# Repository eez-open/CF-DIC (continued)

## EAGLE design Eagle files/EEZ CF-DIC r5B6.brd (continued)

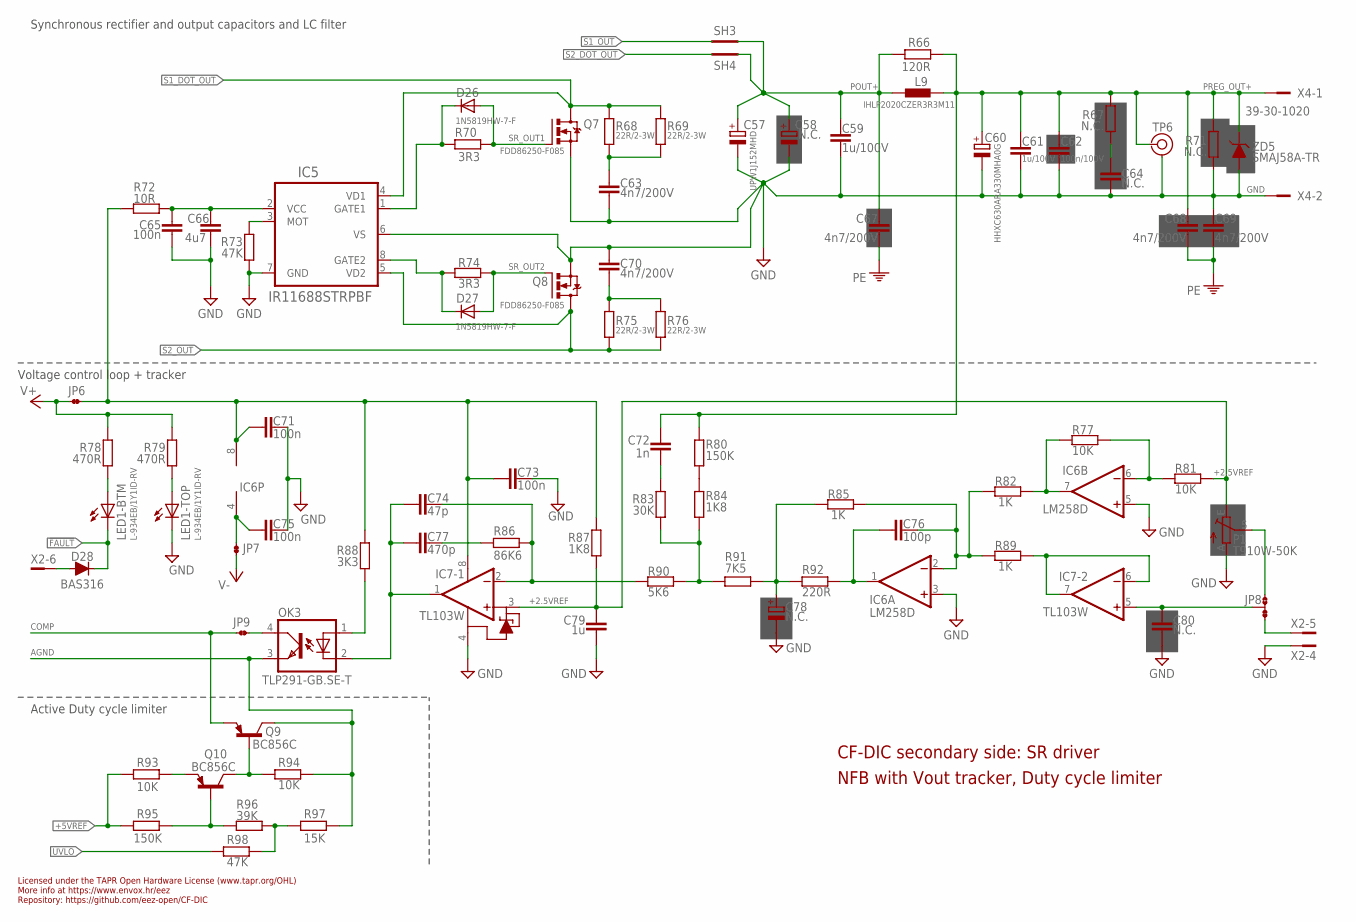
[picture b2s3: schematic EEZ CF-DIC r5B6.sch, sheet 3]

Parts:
C57: UPW1J152MHD; ECAP7.5/18-H35.5-2A
C58: N.C.; ECAP7.5/18
C59, C61: 1u/100V; C1206
C60: HHXC630ARA330MHA0G; CAPAE830X1050N
C62: 100n/100V; C1206
C63, C67, C68, C69, C70: 4n7/200V; C1206
C64: N.C.; C1206
C65, C71, C73, C75: 100n; C0603
C66: 4u7; C1206
C72: 1n; C0805
C74: 47p; C0805
C76: 100p; C0805
C77: 470p; C0805
C78: N.C.; EC1206
C79: 1u; C0805
C80: N.C.; C0805
D26, D27: 1N5819HW-7-F; SOD323-W
D28: BAS316; SOD323-R
IC5: IR11688STRPBF; SO8
IC6: LM258D; SOIC127P600X173-8N
IC7: TL103W; SOIC127P600X173-8N
JP6, JP7, JP9: JP2-NOCUT
JP8: JP3-CUT
L9: IHLP2020CZER3R3M11; IHLP-2020BZ-11
LED1: L-934EB/1Y1ID-RV; L-934EB
OK3: TLP291-GB.SE-T; SO4
P1: T910W-50K; S64W
Q7, Q8: FDD86250-F085; TO263
Q9, Q10: BC856C; SOT23-BEC
R66: 120R; R0805
R67: N.C.; R1210
R68, R69, R75, R76: 22R/2-3W; R2512
R70, R74: 3R3; R0805
R71: N.C.; R2512
R72: 10R; R0805
R73, R98: 47K; R0805
R77, R81, R93, R94: 10K; R0805
R78, R79: 470R; R0805
R80, R95: 150K; R0805
R82, R85, R89: 1K; R0805
R83: 30K; R0805
R84, R87: 1K8; R0805
R86: 86K6; R0805
R88: 3K3; R0805
R90: 5K6; R0805
R91: 7K5; R0805
R92: 220R; R0805
R96: 39K; R0805
R97: 15K; R0805
SH3, SH4: SHORTNOHOLE; SHORT_NOHOLE
TP6: TEST_POINT-2; TP_1.1MM_2
X2: 22-05-7095; SPOX_22-05-7095
X4: 39-30-1020; MINIFIT_39301020
ZD5: SMAJ58A-TR; DO214AC

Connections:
!FAULT: D28.C, LED1.BC (C); also elsewhere on the board
+2.5VREF: C79.1, IC7.3 (+IN1), P1.E, R81.2, R87.1
+5VREF: R93.1, R95.1; also elsewhere on the board
AGND: OK3.3 (EMIT), Q9.C, R94.2, R97.2; also elsewhere on the board
COMP: JP9.1, Q9.E; also elsewhere on the board
GND: C57.-, C58.-, C59.2, C60.-, C61.2, C62.2, C63.2, C64.1, C65.2, C66.2, C69.1, C70.2, C71.2, C73.2, C75.2, C78.-, C79.2, C80.2, IC5.6 (VS), IC5.7 (GND), IC6.3 (+IN), IC6.5 (+IN), IC7.4 (VCC-), LED1.TC (C), P1.A, Q7.2 (S), Q8.2 (S), R71.1, R73.2, TP6.GND, X2.4, X4.2, ZD5.A; also elsewhere on the board
unnamed: D28.A, X2.6
unnamed: C64.2, R67.1
unnamed: C77.2, R86.2
unnamed: C74.2, IC7.2 (-IN1), R86.1, R90.1
unnamed: LED1.TA (A), R79.2
unnamed: R80.1, R84.2
unnamed: LED1.BA (A), R78.2
unnamed: IC5.3 (MOT), R73.1
unnamed: C72.2, R83.2
unnamed: C75.1, IC6.4 (V-), JP7.1
unnamed: JP9.2, OK3.4 (COL)
unnamed: C71.1, C73.1, IC6.8 (V+), IC7.8 (VCC+), JP6.2, R72.1, R87.2, R88.2
unnamed: R83.1, R84.1, R90.2, R91.2
unnamed: IC6.7 (OUT), R77.1, R82.2
unnamed: C80.1, IC7.5 (+IN), JP8.COM
unnamed: JP8.NO, P1.S
unnamed: Q9.B, Q10.C, R94.1
unnamed: Q10.E, R93.2
unnamed: C76.2, IC6.2 (-IN), R82.1, R85.2, R89.1
unnamed: C63.1, R68.2, R69.2
unnamed: C70.1, R75.2, R76.2
unnamed: R96.2, R97.1, R98.1
unnamed: Q10.B, R95.2, R96.1
unnamed: D26.C, IC5.1 (GATE1), R70.2
unnamed: D27.C, IC5.8 (GATE2), R74.2
unnamed: C74.1, C77.1, IC7.1 (OUT1), OK3.2 (C)
unnamed: IC6.6 (-IN), R77.2, R81.1
unnamed: C76.1, IC6.1 (OUT), R92.2
NFB_OFFSET: C78.+, R85.1, R91.1, R92.1
OK_A: OK3.1 (A), R88.1
PE: C67.2, C68.2, C69.2; also elsewhere on the board
POUT+: C57.+, C58.+, C59.1, C67.1, L9.1, R66.1, SH3.P$2 (GND_B), SH4.P$1 (GND_A)
PREG_OUT+: C60.+, C61.1, C62.1, C68.1, C72.1, L9.2, R66.2, R67.2, R71.2, R80.2, TP6.TIP, X4.1, ZD5.C; also elsewhere on the board
S1_DOT_OUT: IC5.4 (VD1), Q7.3 (D), R68.1, R69.1; also elsewhere on the board
S1_OUT: SH3.P$1 (GND_A); also elsewhere on the board
S2_DOT_OUT: SH4.P$2 (GND_B); also elsewhere on the board
S2_OUT: IC5.5 (VD2), Q8.3 (D), R75.1, R76.1; also elsewhere on the board
SR_OUT1: D26.A, Q7.1 (G), R70.1
SR_OUT2: D27.A, Q8.1 (G), R74.1
SYNC_VCC: C65.1, C66.1, IC5.2 (VCC), R72.2
UVLO: R98.2; also elsewhere on the board
U_CTRL: JP8.NC, X2.5
U_MON1: IC7.6 (-IN), IC7.7 (OUT), R89.2
V+: JP6.1, R78.1, R79.1; also elsewhere on the board
V-: JP7.2; also elsewhere on the board

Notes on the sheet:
Licensed under the TAPR Open Hardware License (www.tapr.org/OHL)
Repository: https://github.com/eez-open/CF-DIC
More info at https://www.envox.hr/eez
CF-DIC secondary side: SR driver
NFB with Vout tracker, Duty cycle limiter
Voltage control loop + tracker
Synchronous rectifier and output capacitors and LC filter
Active Duty cycle limiter

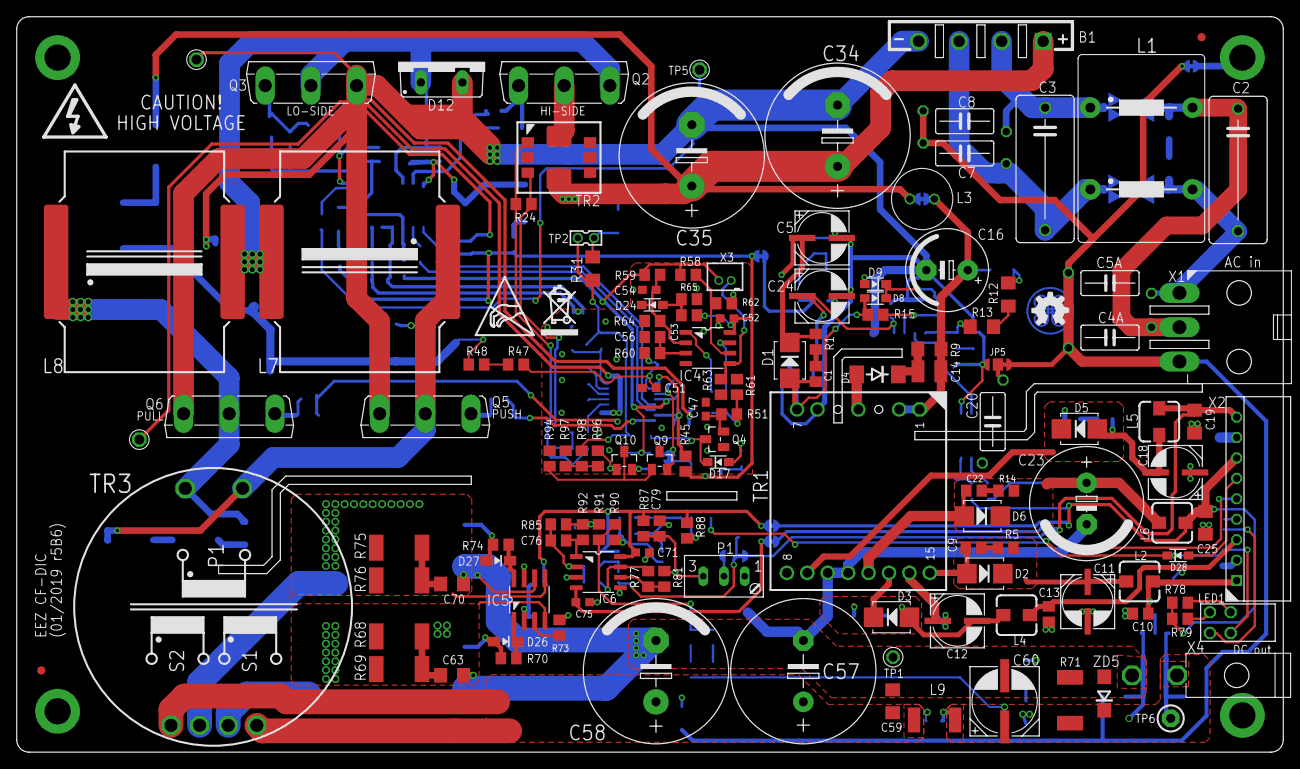
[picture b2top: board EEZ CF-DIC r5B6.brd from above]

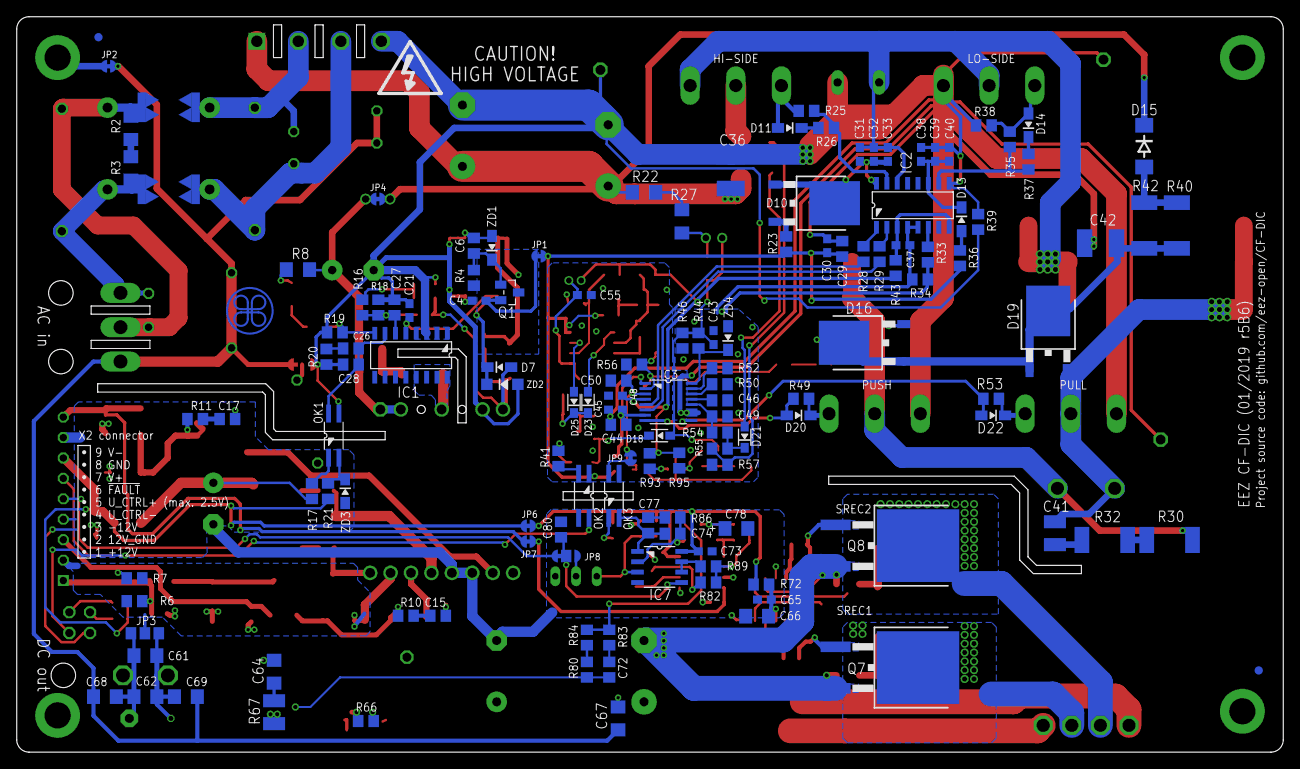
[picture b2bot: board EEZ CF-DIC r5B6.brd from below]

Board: 2 copper layers, 155.0 x 90.0 mm, 278 parts (137 on the bottom side), 147 nets.

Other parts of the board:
EEZ_SIGNATURE: SIGNATURESMALL; SIGNATURE_5MM
U$2: RECYCLE_BIN1/8
U$4: ESD_SYMBOL

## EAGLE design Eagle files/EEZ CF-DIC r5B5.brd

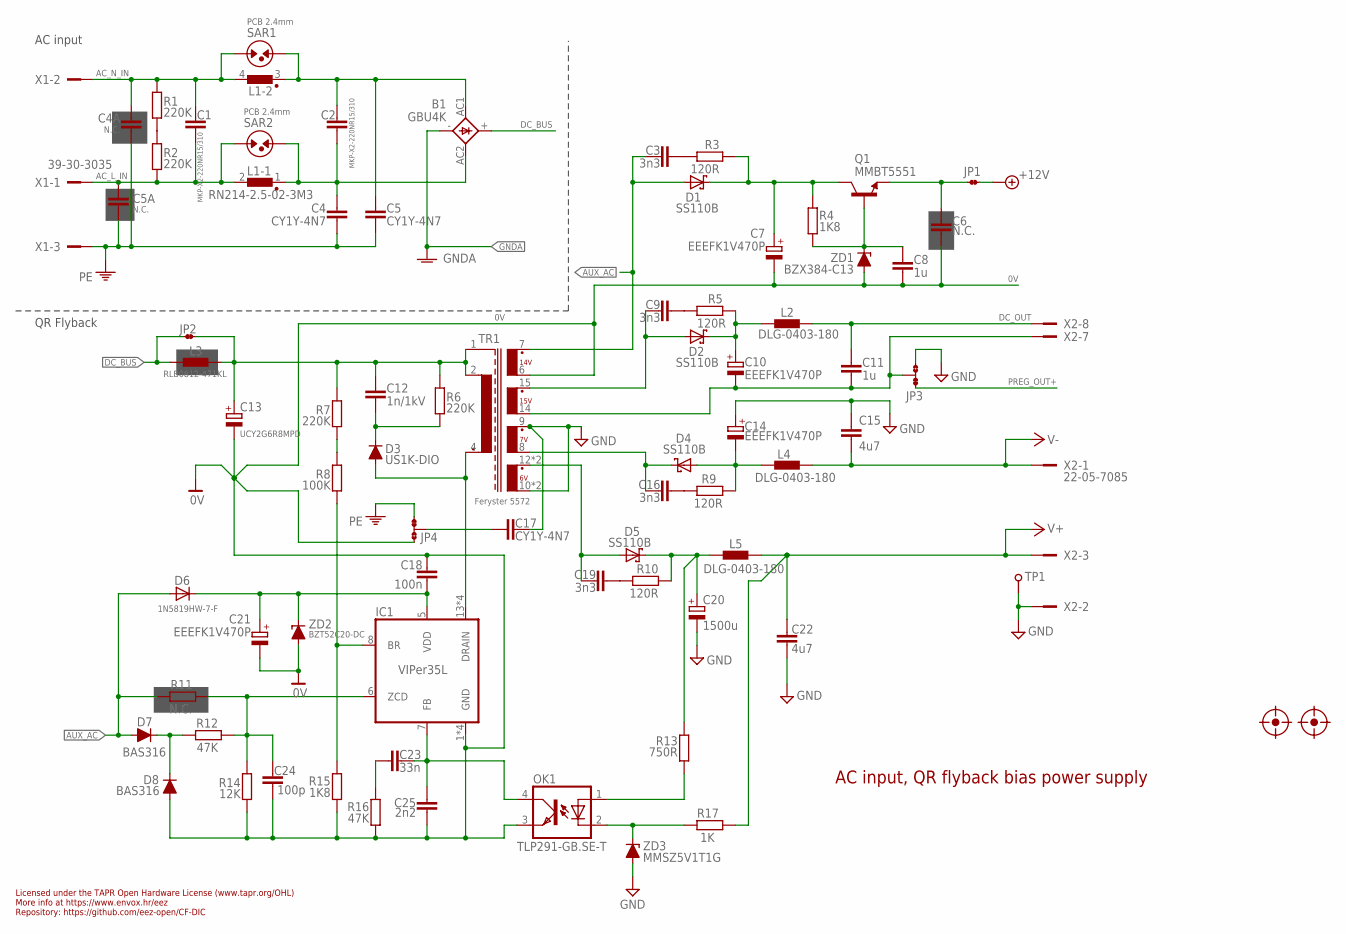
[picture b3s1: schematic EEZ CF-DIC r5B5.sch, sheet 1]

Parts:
B1: GBU4K; GBU4K_CRE
C1, C2: MKP-X2-220NR15/310; C150-072X183
C3, C9, C16, C19: 3n3; C0805
C4, C5, C17: CY1Y-4N7; CY075-032X103
C4A: N.C.; CY075-032X103-ROTATED
C5A: N.C.; CY075-032X103
C6: N.C.; C0603
C7, C10, C14, C21: EEEFK1V470P; CAPAE660X610N
C8, C11: 1u; C0805
C12: 1n/1kV; C1210
C13: UCY2G6R8MPD; ECAP5/10.5
C15, C22: 4u7; C1206
C18: 100n; C0603
C20: 1500u; ECAP5/13
C23: 33n; C0805
C24: 100p; C0805
C25: 2n2; C0805
D1, D2, D4, D5: SS110B; SMB
D3: US1K-DIO; DO214AA
D6: 1N5819HW-7-F; SOD323-W
D7, D8: BAS316; SOD323-R
FM1, FM2: FIDUCIAL_2; FIDUCIAL_DUAL
IC1: VIPer35L; SOIC-16
JP1, JP2: JP2-NOCUT
JP3, JP4: JP3-CUT
L1: RN214-2.5-02-3M3; RN214; FARNELL 1191518
L2, L4, L5: DLG-0403-180; DE0403
L3: RLB0812-471KL; FERSYTER_DSZ6
OK1: TLP291-GB.SE-T; SO4
Q1: MMBT5551; SOT23-BEC
R1, R2, R6, R7: 220K; R1206
R3, R5, R9, R10: 120R; R0805
R4, R15: 1K8; R0805
R8: 100K; R0805
R11: N.C.; R0805
R12, R16: 47K; R0805
R13: 750R; R0805
R14: 12K; R0805
R17: 1K; R0805
SAR1, SAR2: PCB 2.4mm; PCB-SAR_2.4MM
TP1: PCB_TEST_TABSHIELD; PCB_SHIELD_TAB
TR1: Feryster 5572; FERYSTER_5572
X1: 39-30-3035; MINIFIT_6659-3_CRE
X2: 22-05-7085; SPOX_22-05-7085
ZD1: BZX384-C13; SOD323-W
ZD2: BZT52C20-DC; SOD123
ZD3: MMSZ5V1T1G; SOD323-W

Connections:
0V: C6.2, C7.2 (-), C8.2, C13.-, C18.1, C21.2 (-), C24.2, C25.2, D8.A, IC1.1 (GND), IC1.2 (GND), IC1.3 (GND), IC1.4 (GND), JP4.NO, OK1.3 (EMIT), R14.1, R15.2, R16.2, TR1.6 (S_BIAS), ZD1.A, ZD2.A; also elsewhere on the board
6VAC: C19.2, D5.A, TR1.12 (S1_DOT), TR1.13 (S1_DOT)
7VAC: C16.2, D4.C, TR1.8 (S2)
15VAC: C9.2, D2.A, TR1.15 (S3_DOT)
+6V_REC: C20.+, D5.C, L5.1, R10.1, R13.1
+12V: JP1.2; also elsewhere on the board
+15V_REC: C10.1 (+), D2.C, L2.1, R5.1
-7V_REC: C14.2 (-), D4.A, L4.1, R9.1
-15V: C10.2 (-), C11.2, JP3.COM, TR1.14 (S3), X2.7
AC_L_IN: C1.2, C5A.2, L1.2, R2.2, SAR2.1, X1.1
AC_N_IN: C1.1, C4A.2, L1.4 (2), R1.1, SAR1.1, X1.2
AUX_AC: C3.2, D1.A, D6.A, D7.A, R11.2, TR1.7 (S_BIAS_DOT)
AUX_REC: C7.1 (+), D1.C, Q1.C, R3.1, R4.1
DC_BUS: B1.+, JP2.1, L3.P$1 (1); also elsewhere on the board
DC_OUT: C11.1, L2.2, X2.8
FB2: OK1.2 (C), R17.1, ZD3.C
GND: C14.1 (+), C15.1, C17.2, C20.-, C22.2, JP3.NO, TP1.1, TR1.9 (S2_DOT), TR1.10 (S1), TR1.11 (S1), X2.2, ZD3.A; also elsewhere on the board
GNDA: B1.-; also elsewhere on the board
unnamed: C17.1, JP4.COM
unnamed: IC1.8 (BR), R8.2, R15.1
unnamed: C6.1, JP1.1, Q1.E
unnamed: C18.2, C21.1 (+), D6.C, IC1.5 (VDD), ZD2.C
unnamed: R1.2, R2.1
unnamed: B1.AC1, C2.1, C5.2, L1.3 (1), SAR1.2
unnamed: B1.AC2, C2.2, C4.2, L1.1, SAR2.2
unnamed: R7.2, R8.1
unnamed: C8.1, Q1.B, R4.2, ZD1.C
unnamed: OK1.1 (A), R13.2
unnamed: C12.2, D3.C, R6.2
unnamed: C23.2, C25.1, IC1.7 (FB), OK1.4 (COL)
unnamed: C9.1, R5.2
unnamed: C3.1, R3.2
unnamed: C24.1, IC1.6 (ZCD), R11.1, R12.1, R14.2
unnamed: C16.1, R9.2
unnamed: C19.1, R10.2
unnamed: C23.1, R16.1
unnamed: D7.C, D8.C, R12.2
PE: C4.1, C4A.1, C5.1, C5A.1, JP4.NC, X1.3; also elsewhere on the board
PREG_OUT+: JP3.NC; also elsewhere on the board
V+: C22.1, L5.2, R17.2, X2.3; also elsewhere on the board
V-: C15.2, L4.2, X2.1; also elsewhere on the board
VIPER+: C12.1, C13.+, JP2.2, L3.P$2 (2), R6.1, R7.1, TR1.1 (SHIELD), TR1.2
VIPER_D: D3.A, IC1.13 (DRAIN), IC1.14 (DRAIN), IC1.15 (DRAIN), IC1.16 (DRAIN), TR1.4 (P2_DOT)

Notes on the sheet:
Licensed under the TAPR Open Hardware License (www.tapr.org/OHL)
Repository: https://github.com/eez-open/CF-DIC
More info at https://www.envox.hr/eez
AC input, QR flyback bias power supply
QR Flyback
AC input

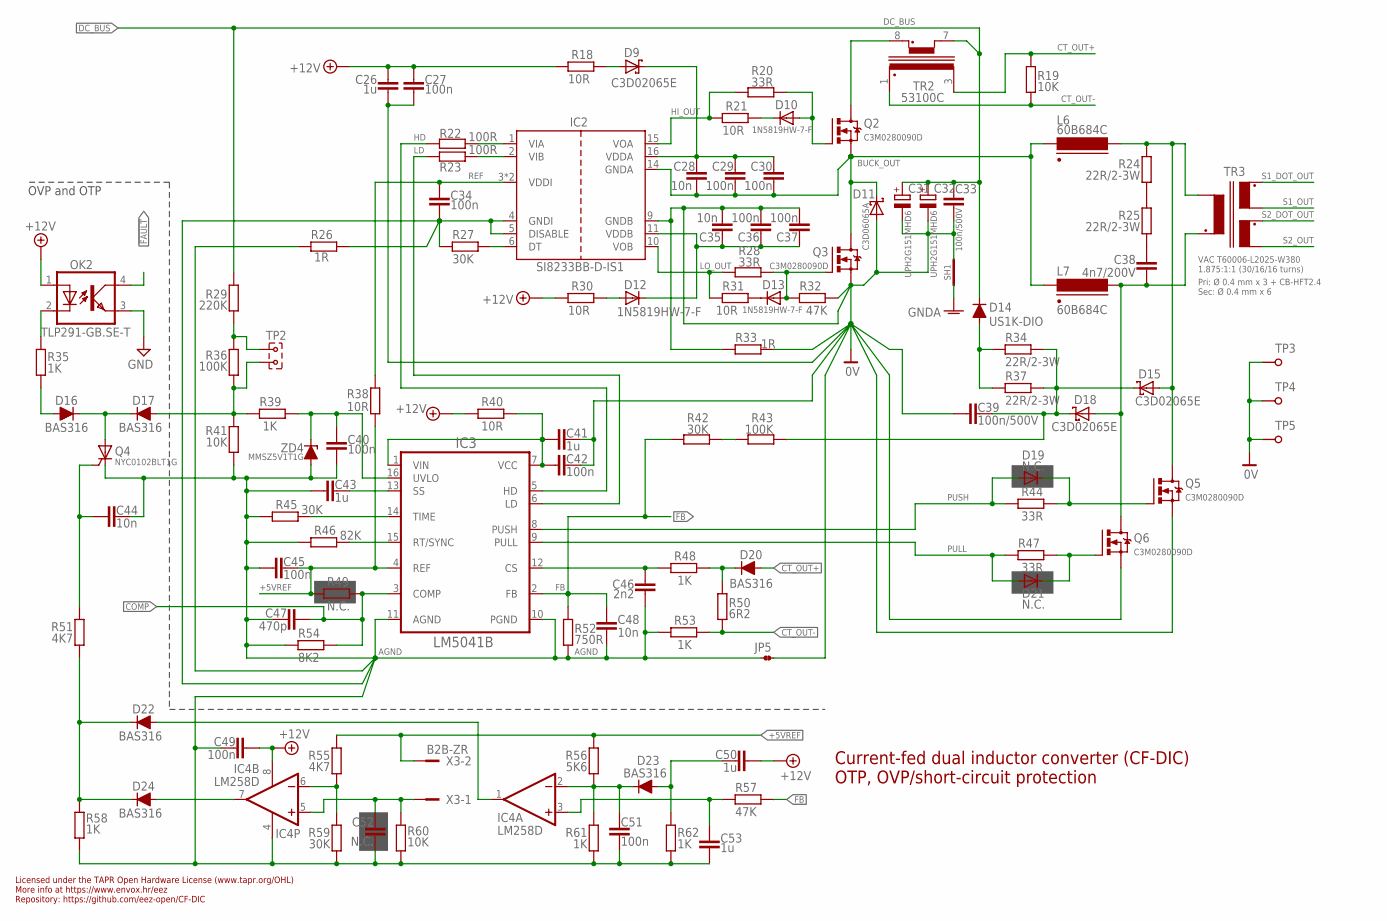
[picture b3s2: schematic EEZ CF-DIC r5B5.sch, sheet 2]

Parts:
C26, C41, C43, C50, C53: 1u; C0805
C27, C29, C30, C34, C36, C37, C40, C42, C45, C49, C51: 100n; C0603
C28, C35, C44, C48: 10n; C0603
C31, C32: UPH2G151MHD6; ECAP7.5/18
C33, C39: 100n/500V; C1812
C38: 4n7/200V; C1210
C46: 2n2; C0805
C47: 470p; C0805
C52: N.C.; C0603
D9, D15, D18: C3D02065E; TO252
D10, D12, D13: 1N5819HW-7-F; SOD323-W
D11: C3D06065A; TO220-2
D14: US1K-DIO; DO214AA
D16, D17, D20, D22, D23, D24: BAS316; SOD323-R
D19, D21: N.C.; SOD323-W
IC2: SI8233BB-D-IS1; SOIC-16
IC3: LM5041B; MTC16
IC4: LM258D; SOIC127P600X173-8N
JP5: JP2-NOCUT
L6, L7: 60B684C; MURATA_6000B
OK2: TLP291-GB.SE-T; SO4
Q2, Q3, Q5, Q6: C3M0280090D; TO247BV
Q4: NYC0102BLT1G; SOT23
R18, R21, R30, R31, R38, R40: 10R; R0805
R19, R41, R60: 10K; R0805
R20, R28, R44, R47: 33R; R0805
R22, R23: 100R; R0805
R24, R25, R34, R37: 22R/2-3W; R2512
R26, R33: 1R; R0805
R27, R42, R45, R59: 30K; R0805
R29: 220K; R1206
R32, R57: 47K; R0805
R35, R39, R48, R53, R58, R61, R62: 1K; R0805
R36, R43: 100K; R0805
R46: 82K; R0805
R49: N.C.; R0805
R50: 6R2; R0805
R51, R55: 4K7; R0805
R52: 750R; R0805
R54: 8K2; R0805
R56: 5K6; R0805
SH1: SHORTNOHOLE; SHORT_NOHOLE
TP2: JUMPER-2PIN-2MM; 2MM-2
TP3, TP4, TP5: TEST-PIN1.2; TEST-PIN_1.2MM
TR2: 53100C; MURATA_5300
TR3: VAC T60006-L2025-W380; VAC_DUAL_SEC
X3: B2B-ZR
ZD4: MMSZ5V1T1G; SOD323-W

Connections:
0V: C26.1, C27.1, C31.-, C32.-, C33.2, C35.2, C36.2, C37.2, C39.1, C41.2, C42.2, D11.2 (A), IC2.9 (GNDB), JP5.2, Q3.S, Q5.S, Q6.S, R32.2, R33.1, R33.2, SH1.P$2 (GND_B), TP3.1, TP4.1, TP5.1; also elsewhere on the board
!FAULT: OK2.4 (COL); also elsewhere on the board
+5VREF: C45.2, IC3.4 (REF), R38.1, R49.1, R55.2, R56.2, X3.2
+12V: C26.2, C27.2, C49.1, C50.1, IC4.8 (V+), OK2.1 (A), R18.2, R30.2, R40.2; also elsewhere on the board
AGND: C34.1, C40.2, C43.1, C44.2, C45.1, C46.1, C47.1, C48.2, C49.2, C51.2, C52.1, C53.1, IC2.4 (GNDI), IC2.5 (DISABLE), IC3.10 (PGND), IC3.11 (AGND), IC4.4 (V-), JP5.1, Q4.1 (C), R26.1, R26.2, R27.1, R41.2, R45.2, R46.2, R52.2, R53.2, R54.1, R58.2, R59.2, R60.2, R61.2, R62.2, ZD4.A; also elsewhere on the board
BUCK_OUT: C28.2, C29.2, C30.2, D11.1 (C), IC2.14 (GNDA), L6.2, L7.2, Q2.S, Q3.D
CLAMP_C: C39.2, D15.1 (C), D15.3 (C), D18.1 (C), D18.3 (C), R34.1, R37.1, R43.2
COMP: C47.2, IC3.3 (COMP), R49.2, R54.2; also elsewhere on the board
CT_OUT+: D20.A, R19.1, TR2.3 (S)
CT_OUT-: R19.2, R50.2, R53.1, TR2.1 (S_DOT)
DC_BUS: C31.+, C32.+, C33.1, D14.C, R29.1, TR2.7; also elsewhere on the board
FB: C48.1, IC3.2 (FB), R42.1, R52.1, R57.1
GND: OK2.3 (EMIT); also elsewhere on the board
GNDA: SH1.P$1 (GND_A); also elsewhere on the board
HD: IC3.5 (HD), R22.2
HI_OUT: IC2.15 (VOA), R20.2, R21.2
LD: IC3.6 (LD), R23.2
LO_OUT: IC2.10 (VOB), R28.1, R31.1
L_PULL: C38.2, D18.2 (A), L7.1, Q6.D, TR3.P1_DOT (P_DOT)
L_PUSH: D15.2 (A), L6.1, Q5.D, R24.2, TR3.P1
unnamed: R29.2, R36.1, TP2.1
unnamed: C28.1, C29.1, C30.1, D9.1 (C), D9.3 (C), IC2.16 (VDDA)
unnamed: R24.1, R25.2
unnamed: C51.1, D23.C, IC4.2 (-IN), R56.1, R61.1
unnamed: D19.C, Q5.G, R44.1
unnamed: D21.C, Q6.G, R47.1
unnamed: Q2.D, TR2.8 (P_DOT)
unnamed: C38.1, R25.1
unnamed: IC3.15 (RT/SYNC), R46.1
unnamed: D10.A, Q2.G, R20.1
unnamed: IC3.14 (TIME), R45.1
unnamed: C43.2, IC3.13 (SS)
unnamed: C40.1, IC3.16 (UVLO), R39.1, ZD4.C
unnamed: IC4.6 (-IN), R55.1, R59.1
unnamed: D13.A, Q3.G, R28.2, R32.1
unnamed: R42.2, R43.1
unnamed: D9.2 (A), R18.1
unnamed: OK2.2 (C), R35.1
unnamed: C53.2, IC4.3 (+IN), R57.2
unnamed: D14.A, R34.2, R37.2
unnamed: IC2.1 (VIA), R22.1
unnamed: C46.2, IC3.12 (CS), R48.2
unnamed: D22.A, IC4.1 (OUT)
unnamed: IC2.2 (VIB), R23.1
unnamed: C52.2, IC4.5 (+IN), R60.1, X3.1
unnamed: D10.C, R21.1
unnamed: D24.A, IC4.7 (OUT)
unnamed: IC2.6 (DT), R27.2
unnamed: D22.C, D24.C, R51.2, R58.1
unnamed: D13.C, R31.2
unnamed: C41.1, C42.1, IC3.1 (VIN), IC3.7 (VCC), R40.1
unnamed: C35.1, C36.1, C37.1, D12.C, IC2.11 (VDDB)
unnamed: D20.C, R48.1, R50.1
unnamed: C50.2, D23.A, R62.1
unnamed: D12.A, R30.1
unnamed: C44.1, Q4.2 (G), R51.1
unnamed: D16.C, D17.C, Q4.3 (A)
unnamed: D16.A, R35.2
PULL: D21.A, IC3.9 (PULL), R47.2
PUSH: D19.A, IC3.8 (PUSH), R44.2
REF: C34.2, IC2.3 (VDDI), IC2.8 (VDDI), R38.2
S1_DOT_OUT: TR3.S1_DOT; also elsewhere on the board
S1_OUT: TR3.S1; also elsewhere on the board
S2_DOT_OUT: TR3.S2_DOT; also elsewhere on the board
S2_OUT: TR3.S2; also elsewhere on the board
ULVO: D17.A, R36.2, R39.2, R41.1, TP2.2

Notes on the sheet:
Licensed under the TAPR Open Hardware License (www.tapr.org/OHL)
Repository: https://github.com/eez-open/CF-DIC
More info at https://www.envox.hr/eez
Current-fed dual inductor converter (CF-DIC) OTP, OVP/short-circuit protection
OVP and OTP
1.875:1:1 (30/16/16 turns)
Pri: Ø 0.4 mm x 3 + CB-HFT2.4
Sec: Ø 0.4 mm x 6

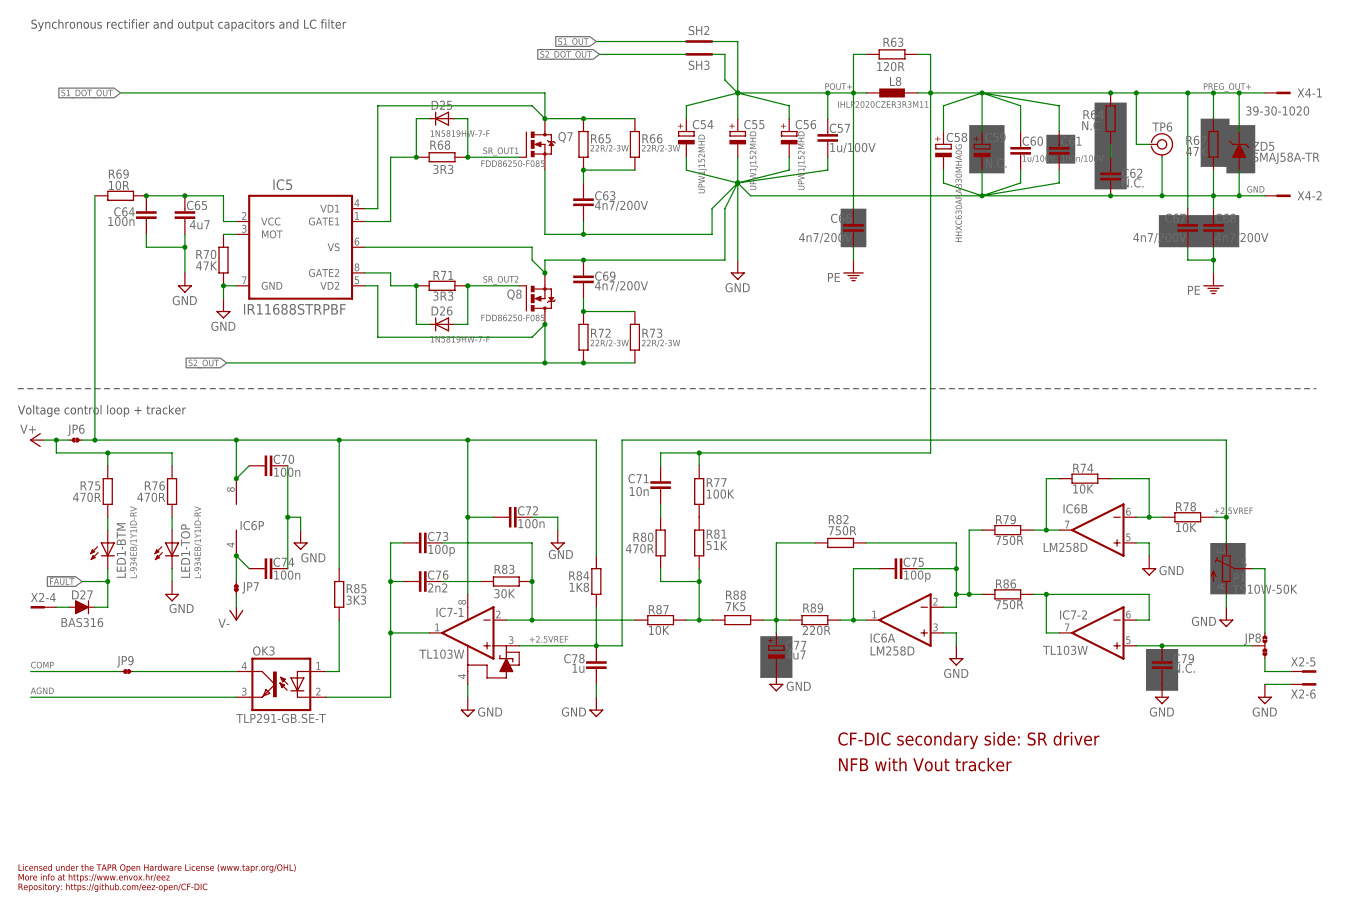
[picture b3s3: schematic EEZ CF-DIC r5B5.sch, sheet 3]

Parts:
C54, C55, C56: UPW1J152MHD; ECAP7.5/18
C57, C60: 1u/100V; C1206
C58: HHXC630ARA330MHA0G; CAPAE830X1050N
C59: N.C.; CAPAE830X1050N
C61: 100n/100V; C1206
C62: N.C.; C1206
C63, C66, C67, C68, C69: 4n7/200V; C1206
C64, C70, C72, C74: 100n; C0603
C65: 4u7; C1206
C71: 10n; C0603
C73, C75: 100p; C0805
C76: 2n2; C0805
C77: 4u7; EC1206
C78: 1u; C0805
C79: N.C.; C0805
D25, D26: 1N5819HW-7-F; SOD323-W
D27: BAS316; SOD323-R
IC5: IR11688STRPBF; SO8
IC6: LM258D; SOIC127P600X173-8N
IC7: TL103W; SOIC127P600X173-8N
JP6, JP7, JP9: JP2-NOCUT
JP8: JP3-CUT
L8: IHLP2020CZER3R3M11; IHLP-2020BZ-11
LED1: L-934EB/1Y1ID-RV; L-934EB
OK3: TLP291-GB.SE-T; SO4
P1: T910W-50K; S64W
Q7, Q8: FDD86250-F085; TO263
R63: 120R; R0805
R64: N.C.; R1210
R65, R66, R72, R73: 22R/2-3W; R2512
R67, R70: 47K; R0805
R68, R71: 3R3; R0805
R69: 10R; R0805
R74, R78, R87: 10K; R0805
R75, R76, R80: 470R; R0805
R77: 100K; R0805
R79, R82, R86: 750R; R0805
R81: 51K; R0805
R83: 30K; R0805
R84: 1K8; R0805
R85: 3K3; R0805
R88: 7K5; R0805
R89: 220R; R0805
SH2, SH3: SHORTNOHOLE; SHORT_NOHOLE
TP6: TEST_POINT-2; TP_1.1MM_2
X2: 22-05-7085; SPOX_22-05-7085
X4: 39-30-1020; MINIFIT_39301020
ZD5: SMAJ58A-TR; DO214AC

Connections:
!FAULT: D27.C, LED1.BC (C); also elsewhere on the board
+2.5VREF: C78.1, IC7.3 (+IN1), P1.E, R78.2, R84.1
AGND: OK3.3 (EMIT); also elsewhere on the board
COMP: JP9.1; also elsewhere on the board
GND: C54.-, C55.-, C56.-, C57.2, C58.-, C59.-, C60.2, C61.2, C62.1, C63.2, C64.2, C65.2, C68.1, C69.2, C70.2, C72.2, C74.2, C77.-, C78.2, C79.2, IC5.6 (VS), IC5.7 (GND), IC6.3 (+IN), IC6.5 (+IN), IC7.4 (VCC-), LED1.TC (C), P1.A, Q7.2 (S), Q8.2 (S), R67.1, R70.2, TP6.GND, X2.6, X4.2, ZD5.A; also elsewhere on the board
unnamed: D27.A, X2.4
unnamed: C64.1, C65.1, IC5.2 (VCC), R69.2
unnamed: C62.2, R64.1
unnamed: C76.2, R83.2
unnamed: C73.2, IC7.2 (-IN1), R83.1, R87.1
unnamed: LED1.TA (A), R76.2
unnamed: R77.1, R81.2
unnamed: LED1.BA (A), R75.2
unnamed: IC5.3 (MOT), R70.1
unnamed: C71.2, R80.2
unnamed: C74.1, IC6.4 (V-), JP7.1
unnamed: JP9.2, OK3.4 (COL)
unnamed: C70.1, C72.1, IC6.8 (V+), IC7.8 (VCC+), JP6.2, R69.1, R84.2, R85.2
unnamed: R80.1, R81.1, R87.2, R88.2
unnamed: IC6.7 (OUT), R74.1, R79.2
unnamed: C79.1, IC7.5 (+IN), JP8.COM
unnamed: JP8.NO, P1.S
unnamed: C75.2, IC6.2 (-IN), R79.1, R82.2, R86.1
unnamed: C63.1, R65.2, R66.2
unnamed: C69.1, R72.2, R73.2
unnamed: D25.C, IC5.1 (GATE1), R68.2
unnamed: D26.C, IC5.8 (GATE2), R71.2
unnamed: C73.1, C76.1, IC7.1 (OUT1), OK3.2 (C)
unnamed: IC6.6 (-IN), R74.2, R78.1
unnamed: C75.1, IC6.1 (OUT), R89.2
NFB_OFFSET: C77.+, R82.1, R88.1, R89.1
OK_A: OK3.1 (A), R85.1
PE: C66.2, C67.2, C68.2; also elsewhere on the board
POUT+: C54.+, C55.+, C56.+, C57.1, C66.1, L8.1, R63.1, SH2.P$2 (GND_B), SH3.P$1 (GND_A)
PREG_OUT+: C58.+, C59.+, C60.1, C61.1, C67.1, C71.1, L8.2, R63.2, R64.2, R67.2, R77.2, TP6.TIP, X4.1, ZD5.C; also elsewhere on the board
S1_DOT_OUT: IC5.4 (VD1), Q7.3 (D), R65.1, R66.1; also elsewhere on the board
S1_OUT: SH2.P$1 (GND_A); also elsewhere on the board
S2_DOT_OUT: SH3.P$2 (GND_B); also elsewhere on the board
S2_OUT: IC5.5 (VD2), Q8.3 (D), R72.1, R73.1; also elsewhere on the board
SR_OUT1: D25.A, Q7.1 (G), R68.1
SR_OUT2: D26.A, Q8.1 (G), R71.1
U_MON: JP8.NC, X2.5
U_MON1: IC7.6 (-IN), IC7.7 (OUT), R86.2
V+: JP6.1, R75.1, R76.1; also elsewhere on the board
V-: JP7.2; also elsewhere on the board

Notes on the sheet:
Licensed under the TAPR Open Hardware License (www.tapr.org/OHL)
Repository: https://github.com/eez-open/CF-DIC
More info at https://www.envox.hr/eez
CF-DIC secondary side: SR driver
NFB with Vout tracker
Voltage control loop + tracker
Synchronous rectifier and output capacitors and LC filter

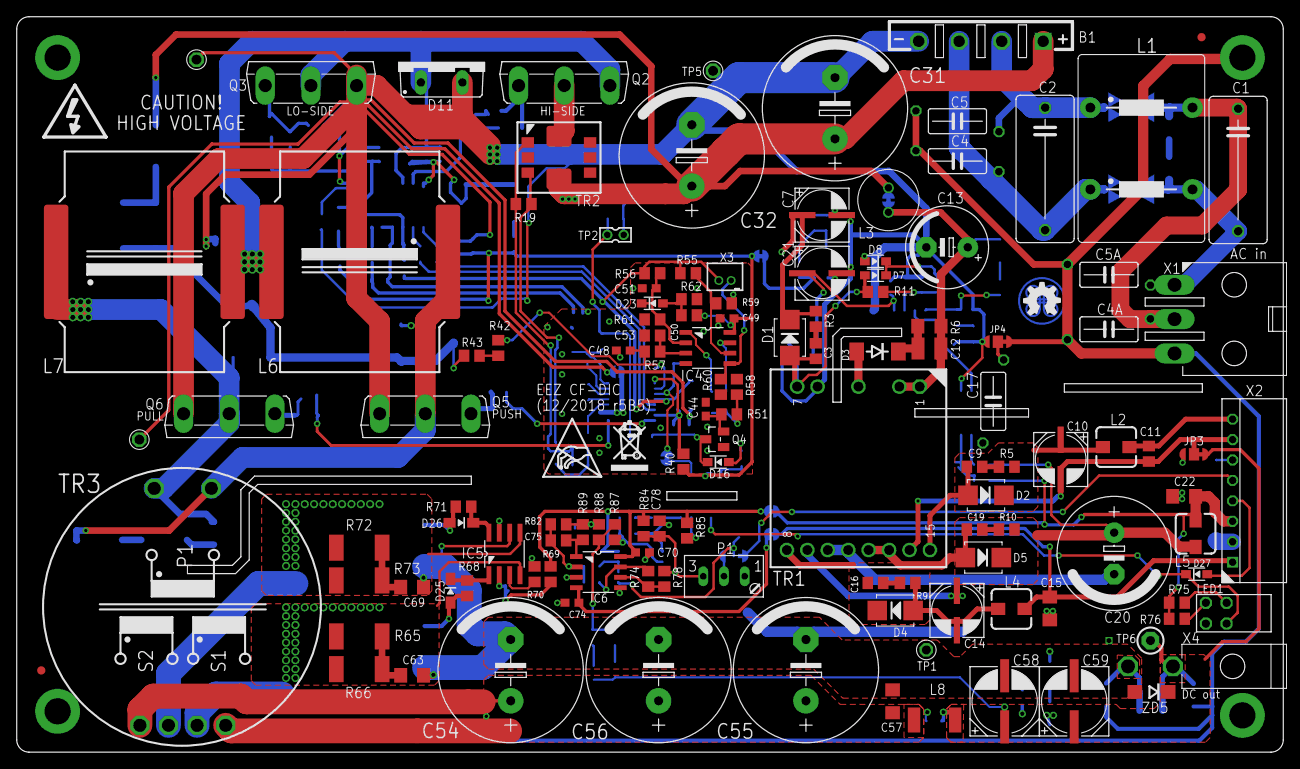
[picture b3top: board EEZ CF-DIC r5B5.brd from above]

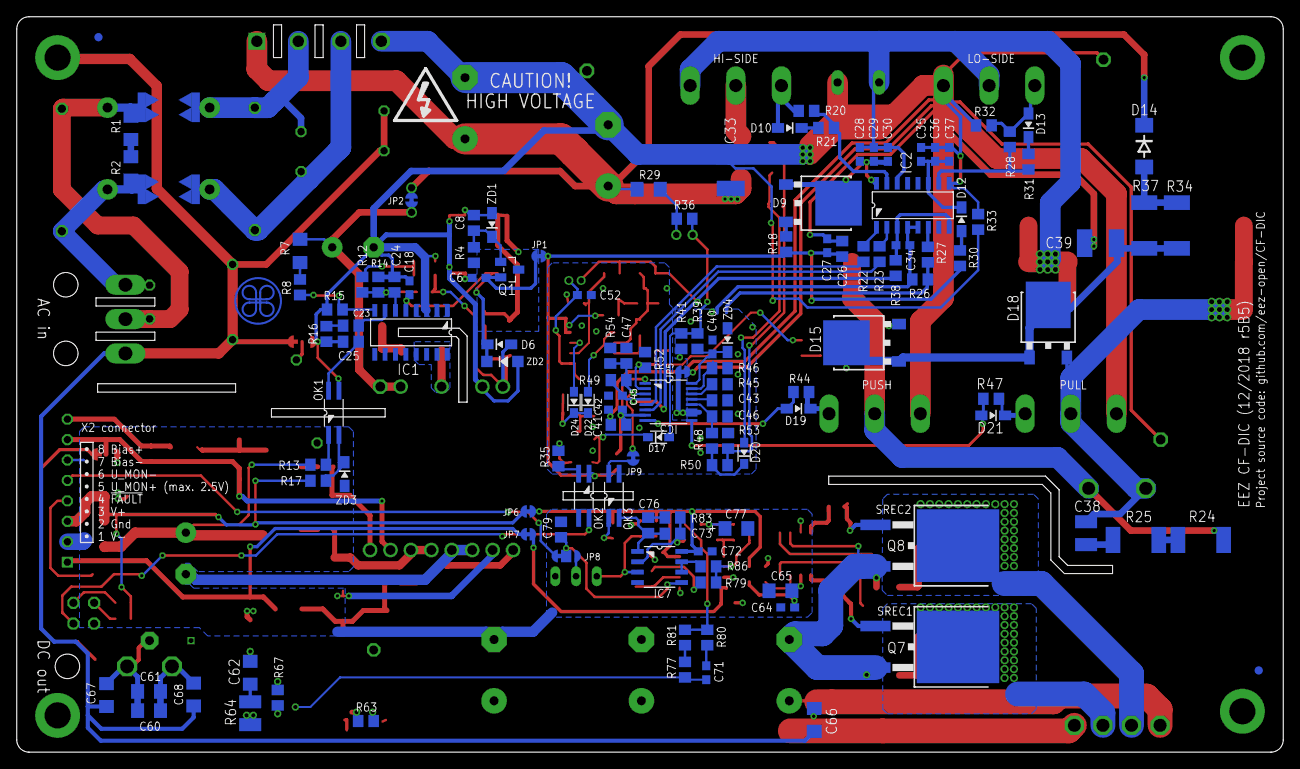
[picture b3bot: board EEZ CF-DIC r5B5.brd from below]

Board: 2 copper layers, 155.0 x 90.0 mm, 263 parts (131 on the bottom side), 137 nets.

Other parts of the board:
EEZ_SIGNATURE: SIGNATURESMALL; SIGNATURE_5MM
U$2: RECYCLE_BIN1/8
U$4: ESD_SYMBOL

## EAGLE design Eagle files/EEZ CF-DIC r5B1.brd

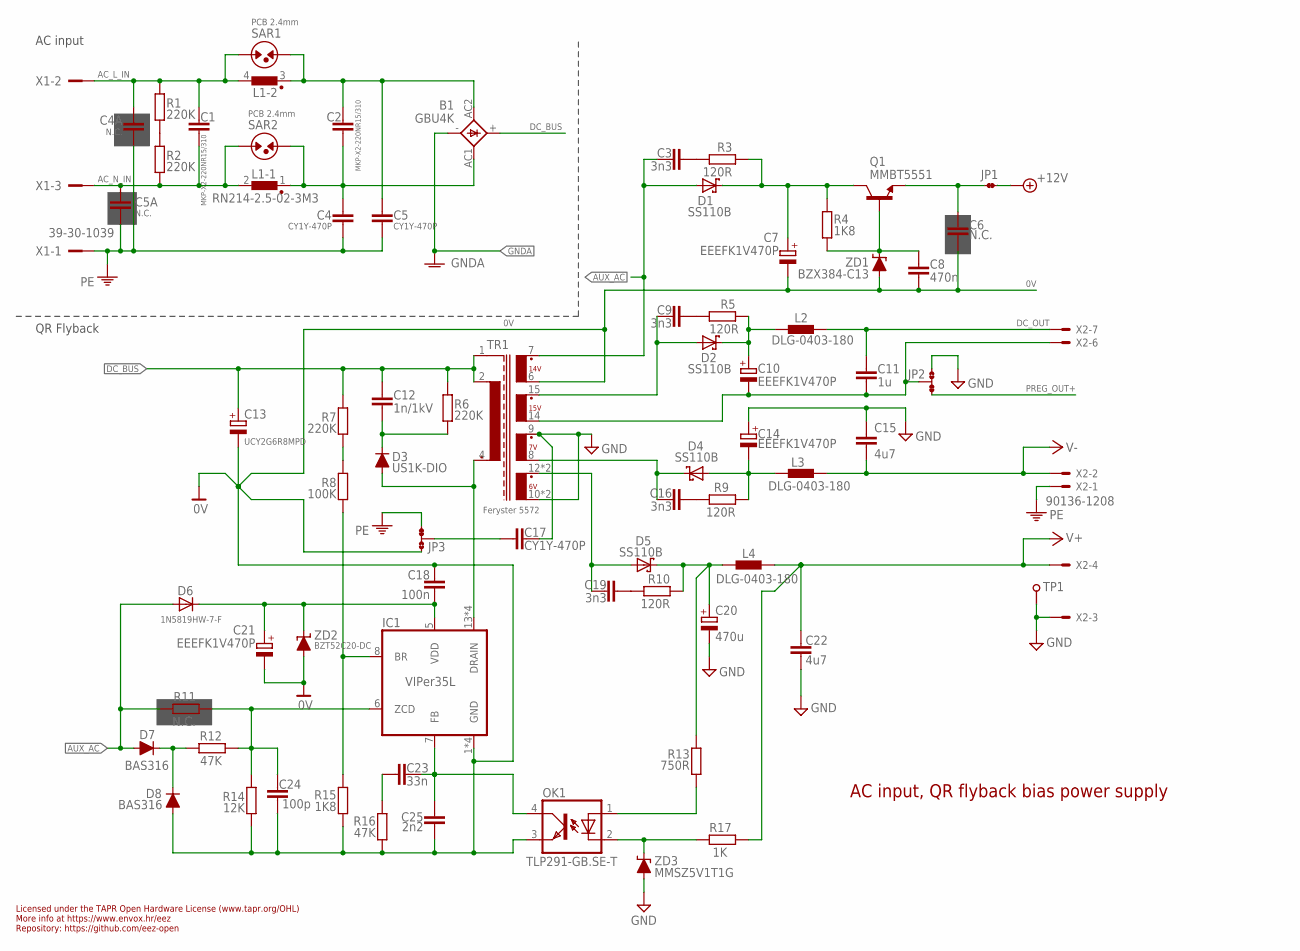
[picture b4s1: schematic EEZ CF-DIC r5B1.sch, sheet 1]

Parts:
B1: GBU4K; GBU4K_CRE
C1, C2: MKP-X2-220NR15/310; C150-072X183
C3, C9, C16, C19: 3n3; C0805
C4, C5, C17: CY1Y-470P; CY075-032X103
C4A, C5A: N.C.; CY075-032X103
C6: N.C.; C0603
C7, C10, C14, C21: EEEFK1V470P; CAPAE660X610N
C8: 470n; C0805
C11: 1u; C0805
C12: 1n/1kV; C1210
C13: UCY2G6R8MPD; ECAP5/10.5
C15, C22: 4u7; C1210
C18: 100n; C0603
C20: 470u; ECAP5/13
C23: 33n; C0805
C24: 100p; C0805
C25: 2n2; C0805
D1, D2, D4, D5: SS110B; SMB
D3: US1K-DIO; DO214AA
D6: 1N5819HW-7-F; SOD323-W
D7, D8: BAS316; SOD323-R
IC1: VIPer35L; SOIC-16
JP1: JP2-NOCUT
JP2, JP3: JP3-CUT
L1: RN214-2.5-02-3M3; RN214; FARNELL 1191518
L2, L3, L4: DLG-0403-180; DE0403
OK1: TLP291-GB.SE-T; SO4
Q1: MMBT5551; SOT23-BEC
R1, R2, R6, R7: 220K; R1206
R3, R5, R9, R10: 120R; R0805
R4, R15: 1K8; R0805
R8: 100K; R0805
R11: N.C.; R0805
R12, R16: 47K; R0805
R13: 750R; R0805
R14: 12K; R0805
R17: 1K; R0805
SAR1, SAR2: PCB 2.4mm; PCB-SAR_2.4MM
TP1: PCB_TEST_TABSHIELD; PCB_SHIELD_TAB
TR1: Feryster 5572; FERYSTER_5572
X1: 39-30-1039; MINIFIT_39301039_CRE
X2: 90136-1208; 70543-08
ZD1: BZX384-C13; SOD323-W
ZD2: BZT52C20-DC; SOD123
ZD3: MMSZ5V1T1G; SOD323-W

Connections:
0V: C6.2, C7.2 (-), C8.2, C13.-, C18.1, C21.2 (-), C24.2, C25.2, D8.A, IC1.1 (GND), IC1.2 (GND), IC1.3 (GND), IC1.4 (GND), JP3.NO, OK1.3 (EMIT), R14.1, R15.2, R16.2, TR1.6 (S_BIAS), ZD1.A, ZD2.A; also elsewhere on the board
6VAC: C19.2, D5.A, TR1.12 (S1_DOT), TR1.13 (S1_DOT)
7VAC: C16.2, D4.C, TR1.8 (S2)
15VAC: C9.2, D2.A, TR1.15 (S3_DOT)
+6V_REC: C20.+, D5.C, L4.1, R10.1, R13.1
+12V: JP1.2; also elsewhere on the board
+15V_REC: C10.1 (+), D2.C, L2.1, R5.1
-7V_REC: C14.2 (-), D4.A, L3.1, R9.1
-15V: C10.2 (-), C11.2, JP2.COM, TR1.14 (S3), X2.6
AC_L_IN: C1.1, C4A.2, L1.4 (2), R1.1, SAR1.1, X1.2
AC_N_IN: C1.2, C5A.2, L1.2, R2.2, SAR2.1, X1.3
AUX_AC: C3.2, D1.A, D6.A, D7.A, R11.2, TR1.7 (S_BIAS_DOT)
AUX_REC: C7.1 (+), D1.C, Q1.C, R3.1, R4.1
DC_BUS: B1.+, C12.1, C13.+, R6.1, R7.1, TR1.1 (SHIELD), TR1.2; also elsewhere on the board
DC_OUT: C11.1, L2.2, X2.7
FB2: OK1.2 (C), R17.1, ZD3.C
GND: C14.1 (+), C15.1, C17.2, C20.-, C22.2, JP2.NO, TP1.1, TR1.9 (S2_DOT), TR1.10 (S1), TR1.11 (S1), X2.3, ZD3.A; also elsewhere on the board
GNDA: B1.-; also elsewhere on the board
unnamed: C17.1, JP3.COM
unnamed: IC1.8 (BR), R8.2, R15.1
unnamed: C6.1, JP1.1, Q1.E
unnamed: C18.2, C21.1 (+), D6.C, IC1.5 (VDD), ZD2.C
unnamed: R1.2, R2.1
unnamed: B1.AC2, C2.1, C5.2, L1.3 (1), SAR1.2
unnamed: B1.AC1, C2.2, C4.2, L1.1, SAR2.2
unnamed: R7.2, R8.1
unnamed: C8.1, Q1.B, R4.2, ZD1.C
unnamed: OK1.1 (A), R13.2
unnamed: C12.2, D3.C, R6.2
unnamed: C23.2, C25.1, IC1.7 (FB), OK1.4 (COL)
unnamed: C9.1, R5.2
unnamed: C3.1, R3.2
unnamed: C24.1, IC1.6 (ZCD), R11.1, R12.1, R14.2
unnamed: C16.1, R9.2
unnamed: C19.1, R10.2
unnamed: C23.1, R16.1
unnamed: D7.C, D8.C, R12.2
PE: C4.1, C4A.1, C5.1, C5A.1, JP3.NC, X1.1, X2.1; also elsewhere on the board
PREG_OUT+: JP2.NC; also elsewhere on the board
V+: C22.1, L4.2, R17.2, X2.4; also elsewhere on the board
V-: C15.2, L3.2, X2.2; also elsewhere on the board
VIPER_D: D3.A, IC1.13 (DRAIN), IC1.14 (DRAIN), IC1.15 (DRAIN), IC1.16 (DRAIN), TR1.4 (P2_DOT)

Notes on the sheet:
Licensed under the TAPR Open Hardware License (www.tapr.org/OHL)
Repository: https://github.com/eez-open
More info at https://www.envox.hr/eez
AC input, QR flyback bias power supply
QR Flyback
AC input
